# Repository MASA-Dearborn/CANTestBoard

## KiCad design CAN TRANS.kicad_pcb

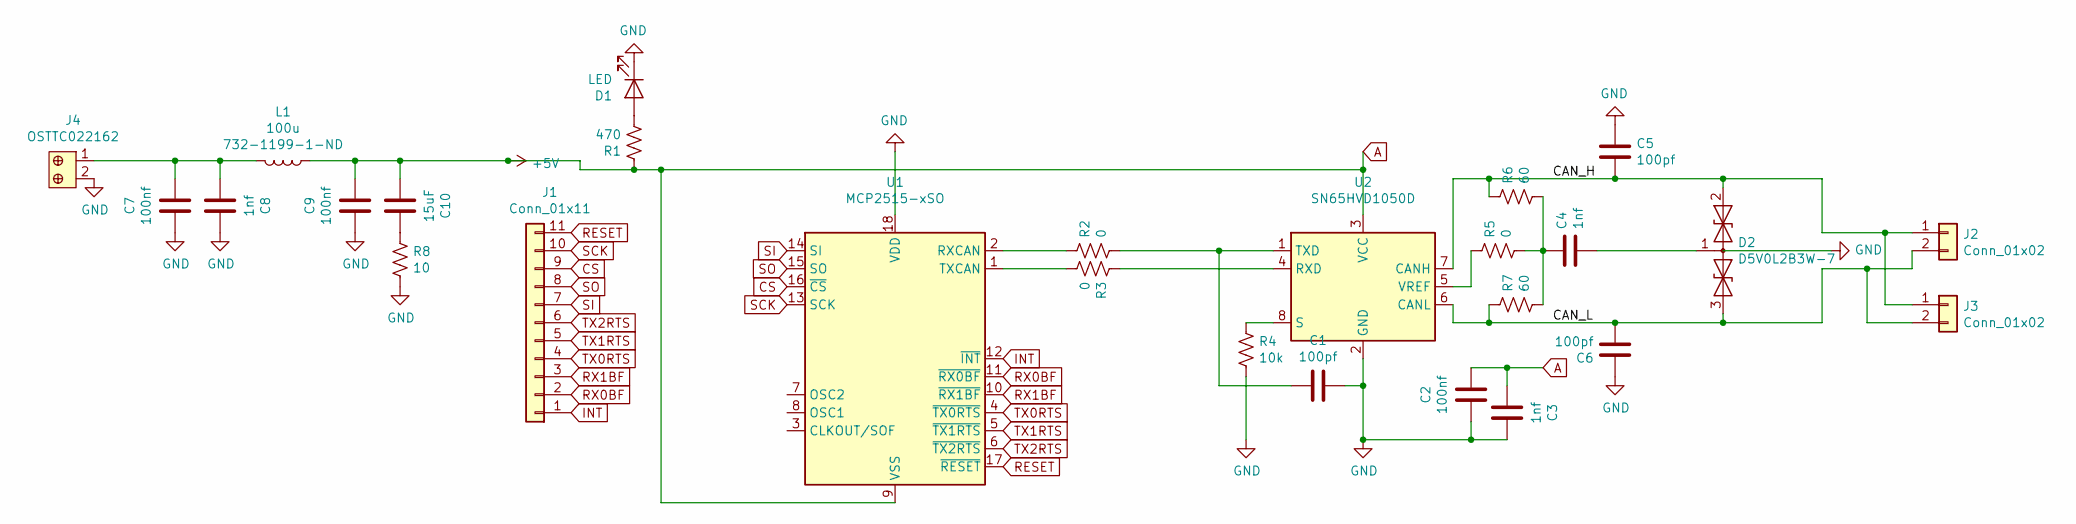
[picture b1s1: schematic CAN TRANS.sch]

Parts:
C1, C5, C6: 100pf; C_0805_2012Metric_Pad1.15x1.40mm_HandSolder
C2, C7, C9: 100nf; C_0805_2012Metric_Pad1.15x1.40mm_HandSolder
C3, C4, C8: 1nf; C_0805_2012Metric_Pad1.15x1.40mm_HandSolder
C10: 15uF; C_0805_2012Metric_Pad1.15x1.40mm_HandSolder
D1: LED; LED_0805_2012Metric_Pad1.15x1.40mm_HandSolder
D2: D5V0L2B3W-7; SOT-23
J1: Conn_01x11; PinHeader_1x11_P2.54mm_Vertical
J2, J3: Conn_01x02; PinHeader_1x02_P2.54mm_Vertical
J4: OSTTC022162; Term_Block_1x2_P5.08MM; MPN OSTTC022162; Digi-Key_PN ED2609-ND
L1: 100u; 744777920; Part # 732-1199-1-ND
R1: 470; R_0805_2012Metric_Pad1.15x1.40mm_HandSolder
R2, R3, R5: 0; R_0805_2012Metric_Pad1.15x1.40mm_HandSolder
R4: 10k; R_0805_2012Metric_Pad1.15x1.40mm_HandSolder
R6, R7: 60; R_0805_2012Metric_Pad1.15x1.40mm_HandSolder
R8: 10; R_0805_2012Metric_Pad1.15x1.40mm_HandSolder
U1: MCP2515-xSO; SOIC-18W_7.5x11.6mm_P1.27mm
U2: SN65HVD1050D; SOIC-8_3.9x4.9mm_P1.27mm

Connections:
/CAN_H: C5.2, D2.2 (A1), J2.1, J3.1, R6.1, U2.7 (CANH)
/CAN_L: C6.2, D2.3 (A2), J2.2, J3.2, R7.1, U2.6 (CANL)
/R2toTXD: C1.2, R2.2, U2.1 (TXD)
/R3toRXD: R3.1, U2.4 (RXD)
/RXCANtoR2: R2.1, U1.2 (RXCAN)
/TXCANtoR3: R3.2, U1.1 (TXCAN)
A: C2.1, C3.2, C9.1, C10.2, L1.1, R1.1, U1.9 (VSS), U2.3 (VCC)
CS: J1.9, U1.16 (~CS)
GND: C1.1, C2.2, C3.1, C5.1, C6.1, C7.2, C8.1, C9.2, D1.1 (K), J4.2, R4.2, R8.2, U1.18 (VDD), U2.2 (GND)
INT: J1.1, U1.12 (~INT)
unnamed: C4.1, R5.2, R6.2, R7.2
unnamed: C4.2, D2.1 (common)
unnamed: C7.1, C8.2, J4.1, L1.2
unnamed: C10.1, R8.1
unnamed: D1.2 (A), R1.2
unnamed: R4.1, U2.8 (S)
unnamed: R5.1, U2.5 (VREF)
RESET: J1.11, U1.17 (~RESET)
RX0BF: J1.2, U1.11 (~RX0BF)
RX1BF: J1.3, U1.10 (~RX1BF)
SCK: J1.10, U1.13 (SCK)
SI: J1.7, U1.14 (SI)
SO: J1.8, U1.15 (SO)
TX0RTS: J1.4, U1.4 (~TX0RTS)
TX1RTS: J1.5, U1.5 (~TX1RTS)
TX2RTS: J1.6, U1.6 (~TX2RTS)

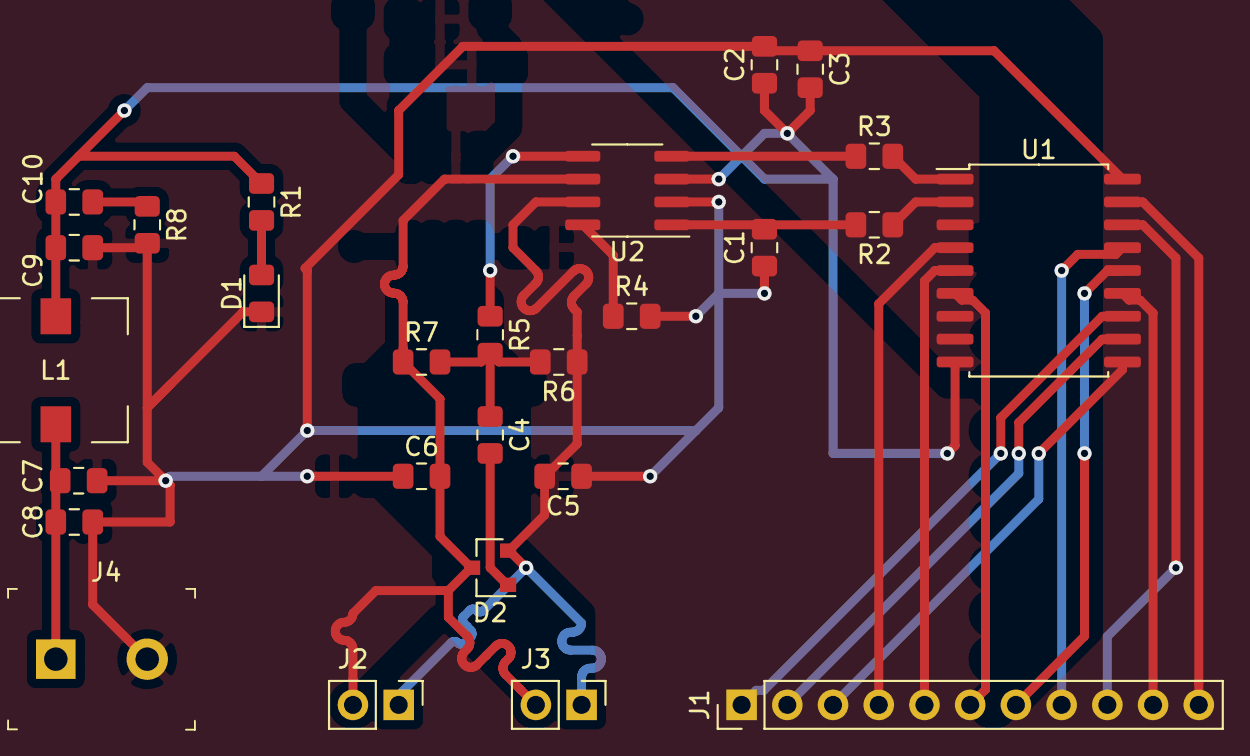
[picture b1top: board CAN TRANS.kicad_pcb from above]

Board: 2 copper layers, 27 parts (0 on the bottom side), 26 nets.

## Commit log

2020-01-31 Initialized with file upload
